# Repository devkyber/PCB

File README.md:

# PCB Copilot

**AI-assisted PCB engineering. Native KiCad. Evidence you can inspect.**

Prepare scoped changes, check the candidate, inspect the native views, and apply
it explicitly. Keep manufacturer evidence and engineering decisions with the
design through to a gated manufacturing package.

**[Get started](docs/QUICKSTART.md)** · **[Explore the examples](examples/README.md)** ·
**[Make an offline handover](docs/HANDOVER.md)** · **[Read the workflow](docs/WORKFLOW.md)**

## Follow a signal through three native boards

*Recorded native CAD renders and schematic captures of unbuilt prototypes.
All three report zero native ERC/DRC violations and zero unconnected items.
The USB-C PPTC body is not modeled. [Source and artifact hashes](docs/media/examples-manifest.json)
bind this gallery to the exact saved designs.*

| Example | Circuit and files | Current engineering boundary |
| --- | --- | --- |
| [USB-C power entry](examples/usb-c-power/README.md) | Six-contact USB4125 power-only connector, independent CC resistors, PPTC and transient shunt. [Schematic](examples/usb-c-power/output/schematic.pdf) · [3D model](examples/usb-c-power/output/usb-c-power.glb) | Native ERC/DRC and parity pass. Manufacturer lands meet the unchanged geometry baseline. Physical fit, protection behavior, assembly and human decisions remain open; no PD or current sensing. |
| [I²C temperature sensor](examples/i2c-sensor/README.md) | MCP9808 MSOP, eight selectable addresses and ALERT. [Schematic](examples/i2c-sensor/output/schematic.pdf) · [3D model](examples/i2c-sensor/output/i2c-sensor.glb) | Native ERC/DRC and parity pass. Bus behavior, physical fit, supplier assembly and human decisions remain open. |
| [RS-485 interface](examples/rs485-interface/README.md) | THVD1450, explicit control defaults and removable termination. [Schematic](examples/rs485-interface/output/schematic.pdf) · [3D model](examples/rs485-interface/output/rs485-interface.glb) | Native ERC/DRC and parity pass. Short bench-link prototype; isolation, surge/EMC and hardware behavior are unqualified. |

Each includes requirements, design basis, local libraries, exact manufacturer
archives, routed copper, native review views and a source-bound artifact
inventory. All remain **unbuilt DRAFTs**. The smaller
[GPIO indicator](examples/gpio-indicator/README.md) remains the first-run example.

The **[browser workbench](https://devkyber.github.io/PCB/)** needs no KiCad or
hardware connection. Search by reference or MPN, choose a numbered pin and
highlight its actual saved net. Inspect native copper, schematic and 3D views
beside the matching source evidence. The simplified net map omits pours and
exact pad shapes; the native copper views retain complete geometry.
[Download it for offline use or rebuild it](docs/EXPLORER.md).

Try the source-backed bring-up tools without hardware:

```sh
python examples/i2c-sensor/bringup.py demo
python examples/rs485-interface/bringup.py demo
```

The [sensor guide](examples/i2c-sensor/BRINGUP.md) covers identity, signed
big-endian temperature decoding, address shunts and ALERT configuration. The
[RS-485 guide](examples/rs485-interface/BRINGUP.md) covers termination load/power
bounds and explicit driver timing around the last UART stop bit. These are
checked calculations and transaction recipes, not recorded bench results.

## Get a first result

Use Git, **Python 3.11+** and
[uv](https://docs.astral.sh/uv/getting-started/installation/):

```sh
git clone https://github.com/devkyber/PCB.git
cd PCB
uv sync
uv run python tools/demo.py
```

The Python-only demo copies GPIO inputs into a new temporary directory, checks
status and archived bytes, and exercises the actual missing-preview rejection.
It prints an inspectable report, transcript and exact command logs while
preserving the saved source. Native ERC/DRC is separate.

Try a larger example with `--project examples/rs485-interface`. With **KiCad 10**
and its `pcbnew` Python bindings installed:

```sh
uv run pcb-copilot doctor
uv run python tools/demo.py --project examples/rs485-interface --full
```

A completed review with blockers returns **1** and preserves its findings.
[Quickstart](docs/QUICKSTART.md) covers setup, exit meanings and discovery.

## Hand an engineer an inspectable review

```sh
uv run pcb-copilot report examples/i2c-sensor --output NEW_EXTERNAL_DIRECTORY
uv run pcb-copilot verify-report NEW_EXTERNAL_DIRECTORY --project examples/i2c-sensor
```

Open the generated `index.html` offline. It includes every native schematic
page, assembly and mirrored copper views, the full review, check scopes and
source hashes. Filter findings, enlarge a view, and download the embedded vector
PDF. The packet's manifest also binds the original artifacts.

Verification runs without KiCad and distinguishes intact packet bytes from
whether the current project still matches. Viewing or verifying creates no
approval. See [the handover guide](docs/HANDOVER.md) and the recorded
[GPIO](docs/demos/gpio-review/index.html),
[sensor](docs/demos/i2c-review/index.html),
[RS-485](docs/demos/rs485-review/index.html) and
[USB-C](docs/demos/usb-c-review/index.html) packets.
Download the HTML to run it; GitHub displays its source.

## Inspect a successful change and a rejected stale apply

```sh
uv run python tools/demo_change.py
```

This prepares a real successful preview, changes the external candidate to
exercise stale-apply rejection, then creates a fresh preview. Inspect every
printed PDF page and use its exact hash-bound resume command to apply the
title-block revision to the disposable copy. Native electrical inventories,
PCB bytes and original source hashes are compared.
[The completed proof](docs/media/change-proof.md) records the actual
preview → stale rejection → fresh preview → reviewed apply sequence.

The [fault evaluation](docs/EVALUATION.md) tests corrupted evidence, changed
footprint geometry/model bytes, part identity, and independent candidate/source/
rule changes after genuine native previews:

```sh
uv run python tools/evaluate.py
uv run python tools/evaluate.py --native
uv run python tools/check_examples.py
```

Each case records its actual interface, diagnostic, exit and preservation
hashes. Native cases are explicitly skipped in quick mode. The example checker
verifies archives, selected-part coverage, footprint lineage and recorded
artifact identities; it does not rerun native qualification.

## Why this pipeline

| Engineering need | Implemented behavior |
| --- | --- |
| Preserve engineer-edited CAD | Start with saved native files. Scoped candidates preserve unrelated objects, UUIDs and routed copper. |
| Check where a part came from | Archive exact source bytes and verify selected MPNs, pad maps and local footprint/model receipts. |
| Inspect before installing | Preview with native-tool checks. Apply must match the current successful preview and all bound inputs. |
| Make review portable | Generate an offline handover with native views, complete findings and explicit check limits. |
| Keep decisions current | Bind named human decisions to CAD, requirements, rules and evidence; changed inputs invalidate them. |
| Preserve output during publication | Recheck sources and publish complete packages transactionally. Reject linked publication paths and retain recovery data when rollback cannot finish. |

```text
Saved KiCad + source evidence
             ↓
      Scoped candidate
             ↓
 Checks + native visual inspection
             ↓
       Explicit apply
             ↓
 Current human decisions → gated release
```

## Scope today

Native candidate preview/apply, evidence archive verification, exact supplier
part import, fourteen registered review checks, portable handovers and gated
manufacturing export are implemented. Optional autorouting needs Freerouting
and compatible Java; a route remains a candidate for review.

Agents can operate the CLI. A packaged interactive copilot/MCP service is future
work. Intent generation proposes a redraw and does not merge later manual CAD
edits. Autonomous engineering and measured time savings remain unproven.

The geometric house-rule checker covers portions of **4 of 42** historical
rule sections. ERC, DRC, parity and source hashes establish their stated scope;
circuit choices, thermal/RF/mechanical behavior, bench work and release decisions
still require engineering review. See [limitations](docs/LIMITATIONS.md).

## Use it with your project

Start with [the new-board workflow](docs/WORKFLOW.md#start-a-new-board) and
`templates/project/`. For an existing design, save and close KiCad, prepare a
separate native candidate and preview before using the identical command with
`--apply`. The [complete workflow](docs/WORKFLOW.md) covers layout, supplier
assembly, sign-off and recovery.

Read [Rover PDB](projects/rover-pdb/README.md) and [TMS](projects/tms/README.md)
for those owner projects' recorded status. Their saved CAD and requested scope
remain separate from the educational examples. Frozen boards under
`tests/fixtures/boards` are regression inputs.

| Read | Purpose |
| --- | --- |
| [Quickstart](docs/QUICKSTART.md) | Setup and first useful result |
| [Example catalog](examples/README.md) | Circuits, assumptions and native artifacts |
| [Interactive explorer](docs/EXPLORER.md) | Follow native pads/nets, inspect views and source evidence |
| [Handover](docs/HANDOVER.md) | Generate and verify offline review packets |
| [Workflow](docs/WORKFLOW.md) | Preview, apply, review and release |
| [Architecture](docs/ARCHITECTURE.md) | Ownership and implementation boundaries |
| [Design rules](docs/DESIGN_RULES.md) | Drawing, layout and review conventions |
| [Fault evaluation](docs/EVALUATION.md) | Reproduce the declared regression cases |
| [Roadmap](docs/ROADMAP.md) | Next capabilities and acceptance evidence |
| [Media sources](docs/media/README.md) | Reproduce the images and video |

If the workflow is useful, a star helps other engineers discover it.

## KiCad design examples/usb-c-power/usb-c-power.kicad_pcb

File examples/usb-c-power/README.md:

# USB-C 5 V bench power entry

An **unbuilt educational DRAFT** with independent CC pull-downs, a resettable
fuse, a unidirectional TVS, a power LED and a two-pin output. The
60 × 40 mm two-layer board is fully routed. Revision B replaces the original
connector with the six-contact, power-only GCT USB4125-GF-A: native ERC and
refilled DRC now report zero findings under the unchanged manufacturing rules.
Actual assembly, physical fit and hardware behavior remain unqualified.

Open [usb-c-power.kicad_pro](usb-c-power.kicad_pro) in KiCad 10, or inspect the
[schematic PDF](output/schematic.pdf), [schematic image](output/schematic.png),
[assembly drawing](output/assembly.png), [front copper](output/top-copper.png),
[mirrored underside](output/bottom-copper.png) and [native GLB](output/usb-c-power.glb).
F1 intentionally has no 3D body model. The other package models are exact
archived KiCad library models; none qualifies the selected part's physical fit.

From the repository root:

```sh
uv run pcb-copilot status examples/usb-c-power
uv run pcb-copilot research examples/usb-c-power --verify
uv run pcb-copilot research examples/usb-c-power --verify-schematic-parts
uv run pcb-copilot review examples/usb-c-power --format json
```

The review returns **exit 1**. The dated [actual review](output/review-b.json)
reports clean native ERC/refilled DRC, exact schematic/PCB part/pin-net/UUID
parity and zero unrouted connections. The former eight connector errors were
resolved by selecting compatible manufacturer geometry: 0.25 mm shell rings
and no locating-peg holes. No rule was relaxed, finding excluded, contact land
trimmed, reference waiver added, or human approval invented. Supplier assembly
contracts, the F1 body model and all six human decisions remain unresolved.

Use only a separately qualified **4.75–5.25 V bench source and at most 500 mA
total board-plus-load budget near 23 °C**. Passive 5.1 kOhm CC pull-downs do not
negotiate PD or establish permission to draw 500 mA from every USB port. There
is no source-current detector, active current limiter, reverse blocking,
output regulator or inrush controller. Never backfeed J2. Its pin1 is VOUT and
pin2 is GND; VOUT includes fuse/connector/copper voltage loss.

The selected 0.75 A hold PPTC is **not a 500 mA current limiter**. The TVS has
6 V standoff and a listed 10.3 V maximum clamp at its specified pulse test;
it does **not** provide 5 V overvoltage protection for sensitive loads. Start
with a non-sensitive resistive dummy load and current-limited source. Reflow
is required for the selected PPTC assembly plan. The [design basis](DESIGN_BASIS.md)
records exact manufacturer limits, calculations, pad mapping and open tests.

[Evidence](evidence/index.yaml) archives all selected purchased-part PDFs,
the dated USB integration reference and a pinned Adafruit open-hardware
schematic/board pair for comparison. The [reference review](REFERENCE_REVIEW.md)
states the adopted pattern and differences. The [official-copy receipt](libs/PROVENANCE.json)
and separate [Bourns drawing receipt](libs/footprint-provenance.yaml) pass their
scoped lineage checks. Bourns' recommended PPTC lands differ from generic
1812 pads, so F1 uses an explicitly derived footprint. The replacement USB4125
uses exact official footprint/model copies. All other footprints, every existing
via and unrelated tracks are preserved; J1's local escapes are routed to its
actual six contact positions.

[SOURCE.json](output/SOURCE.json) binds the retained outputs, exact saved
inputs, native version and raw command logs. Checks and renders ran on an
external disposable copy, with source and snapshot input hashes unchanged.
The [author review](docs/review/B_REVIEW.md) records actual page and layout
inspection; it is not an owner sign-off or a hardware qualification.

Saved native CAD is authoritative. Use a separate copy for experiments and
the [shared candidate workflow](../../docs/WORKFLOW.md) for revisions. No owner
board, existing example CAD or frozen test fixture was used as this design's
starting circuit or layout.

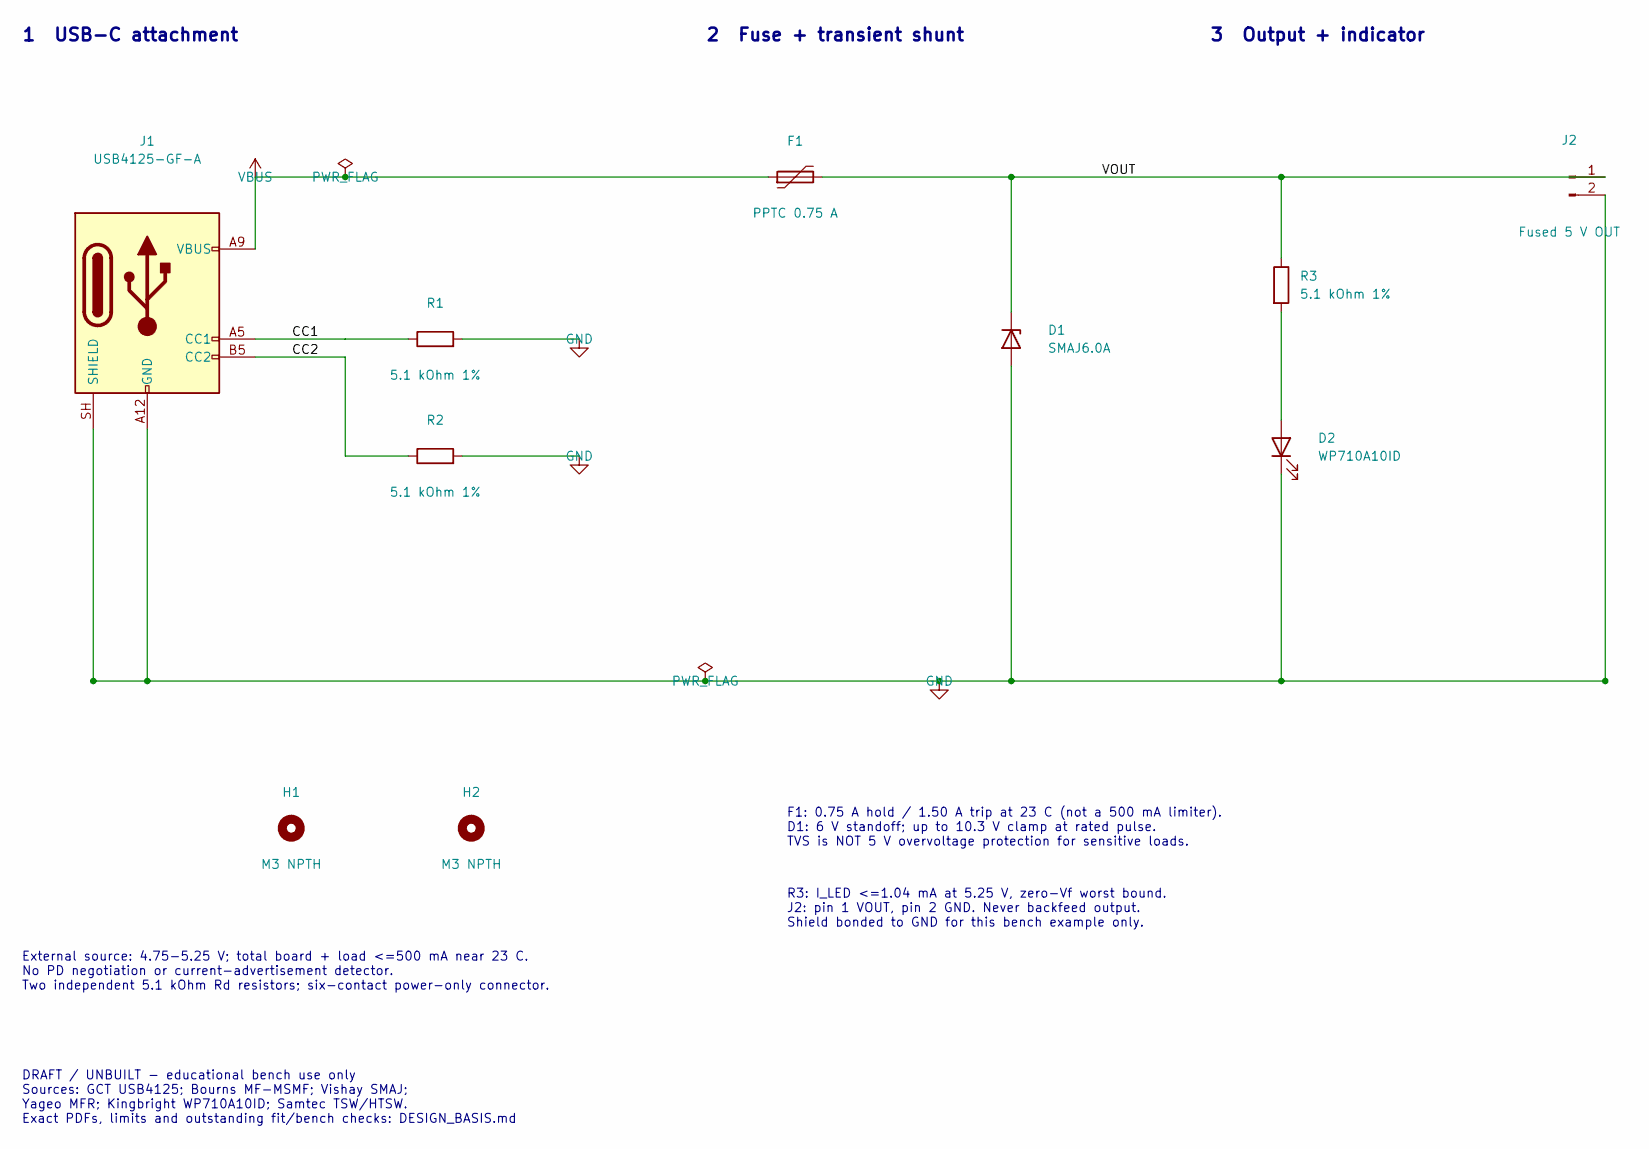
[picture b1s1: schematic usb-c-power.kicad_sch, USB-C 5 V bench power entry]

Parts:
D1: SMAJ6.0A; D_SMA; MPN SMAJ6.0A
D2: WP710A10ID; LED_D3.0mm; MPN WP710A10ID
F1: PPTC 0.75 A; MF-MSMF075_1812_Style1; MPN MF-MSMF075-2
H1, H2: M3 NPTH; MountingHole_3.2mm_M3
J1: USB4125-GF-A; USB_C_Receptacle_GCT_USB4125-xx-x_6P_TopMnt_Horizontal; MPN USB4125-GF-A
J2: Fused 5 V OUT; PinHeader_1x02_P2.54mm_Vertical; MPN HTSW-102-07-G-S
R1, R2, R3: 5.1 kOhm 1%; R_Axial_DIN0207_L6.3mm_D2.5mm_P10.16mm_Horizontal; MPN MFR-25FBF52-5K1

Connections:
CC1: J1.A5 (CC1), R1.1
CC2: J1.B5 (CC2), R2.1
GND: D1.2 (A), D2.1 (K), J1.A12 (GND), J1.B12 (GND), J1.SH (SHIELD), J2.2, R1.2, R2.2
unnamed: D2.2 (A), R3.2
VBUS: F1.1, J1.A9 (VBUS), J1.B9 (VBUS)
VOUT: D1.1 (K), F1.2, J2.1, R3.1

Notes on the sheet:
1 USB-C attachment
2 Fuse + transient shunt
3 Output + indicator
External source: 4.75-5.25 V; total board + load <=500 mA near 23 C. No PD negotiation or current-advertisement detector. Two independent 5.1 kOhm Rd resistors; six-contact power-only connector.
F1: 0.75 A hold / 1.50 A trip at 23 C (not a 500 mA limiter). D1: 6 V standoff; up to 10.3 V clamp at rated pulse. TVS is NOT 5 V overvoltage protection for sensitive loads.
R3: I_LED <=1.04 mA at 5.25 V, zero-Vf worst bound. J2: pin 1 VOUT, pin 2 GND. Never backfeed output. Shield bonded to GND for this bench example only.
DRAFT / UNBUILT - educational bench use only Sources: GCT USB4125; Bourns MF-MSMF; Vishay SMAJ; Yageo MFR; Kingbright WP710A10ID; Samtec TSW/HTSW. Exact PDFs, limits and outstanding fit/bench checks: DESIGN_BASIS.md

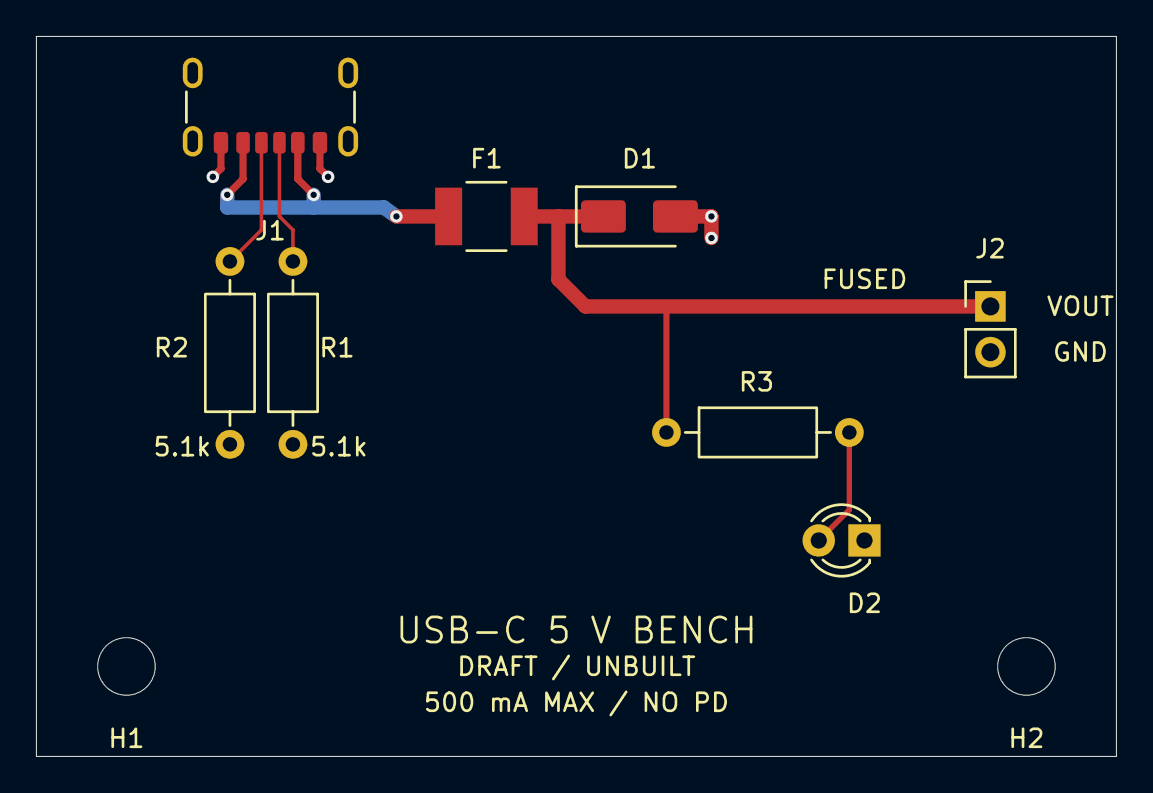
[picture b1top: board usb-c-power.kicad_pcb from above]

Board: 2 copper layers, 60.0 x 40.0 mm, 10 parts (0 on the bottom side), 6 nets.

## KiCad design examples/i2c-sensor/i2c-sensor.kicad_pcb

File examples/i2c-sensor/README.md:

# I2C temperature sensor

An editable 3.3 V MCP9808 MSOP breakout: eight selectable I2C addresses, a local ceramic bypass, fixed bus pullups and a separate open-drain ALERT header. Unbuilt DRAFT; no owner or fabrication approval.

[Start with the register bring-up guide](BRINGUP.md): decode MSB-first signed
temperature words, verify identity/address, and produce a checked ALERT write
recipe. Run the CLI from the repository root; it works offline with no hardware dependency:

```sh
python examples/i2c-sensor/bringup.py decode 0194
python examples/i2c-sensor/bringup.py address --a0 1 --a2 1
```

The example bytes decode to +25.25 C and address 0x1D. These are software
examples, not readings from this unbuilt board. A small read-only bus adapter is
provided for an explicitly configured host; locked settings and malformed reads
are rejected rather than silently accepted.

J1 is 3V3 / GND / SCL / SDA. JP1..3 select A0..A2; no shunts gives 0x18. Power off before changing address shunts. Start at 100 kHz and assess the real host's voltage, combined pullups and measured bus rise time. ALERT requires firmware configuration after reset.

The root KiCad files are the editable design. REQUIREMENTS.md defines the operating assumptions; DESIGN_BASIS.md records exact source decisions and calculations. evidence/index.yaml binds archived primary manufacturer bytes. Local official KiCad library copies, models and license/source receipts are in libs/. Generic mechanical models and a clean native check do not qualify physical fit, temperature accuracy or assembly.

```powershell
uv run pcb-copilot review examples/i2c-sensor
uv run pcb-copilot report examples/i2c-sensor --output C:/Temp/i2c-sensor-handover
```

Retained native views/check results in output/ are bound to declared source hashes by SOURCE.json. Any source change requires fresh checks and views. Full review deliberately remains blocked by unsigned human decisions and missing supplier assembly contracts. No fabrication outputs or bench results are included.

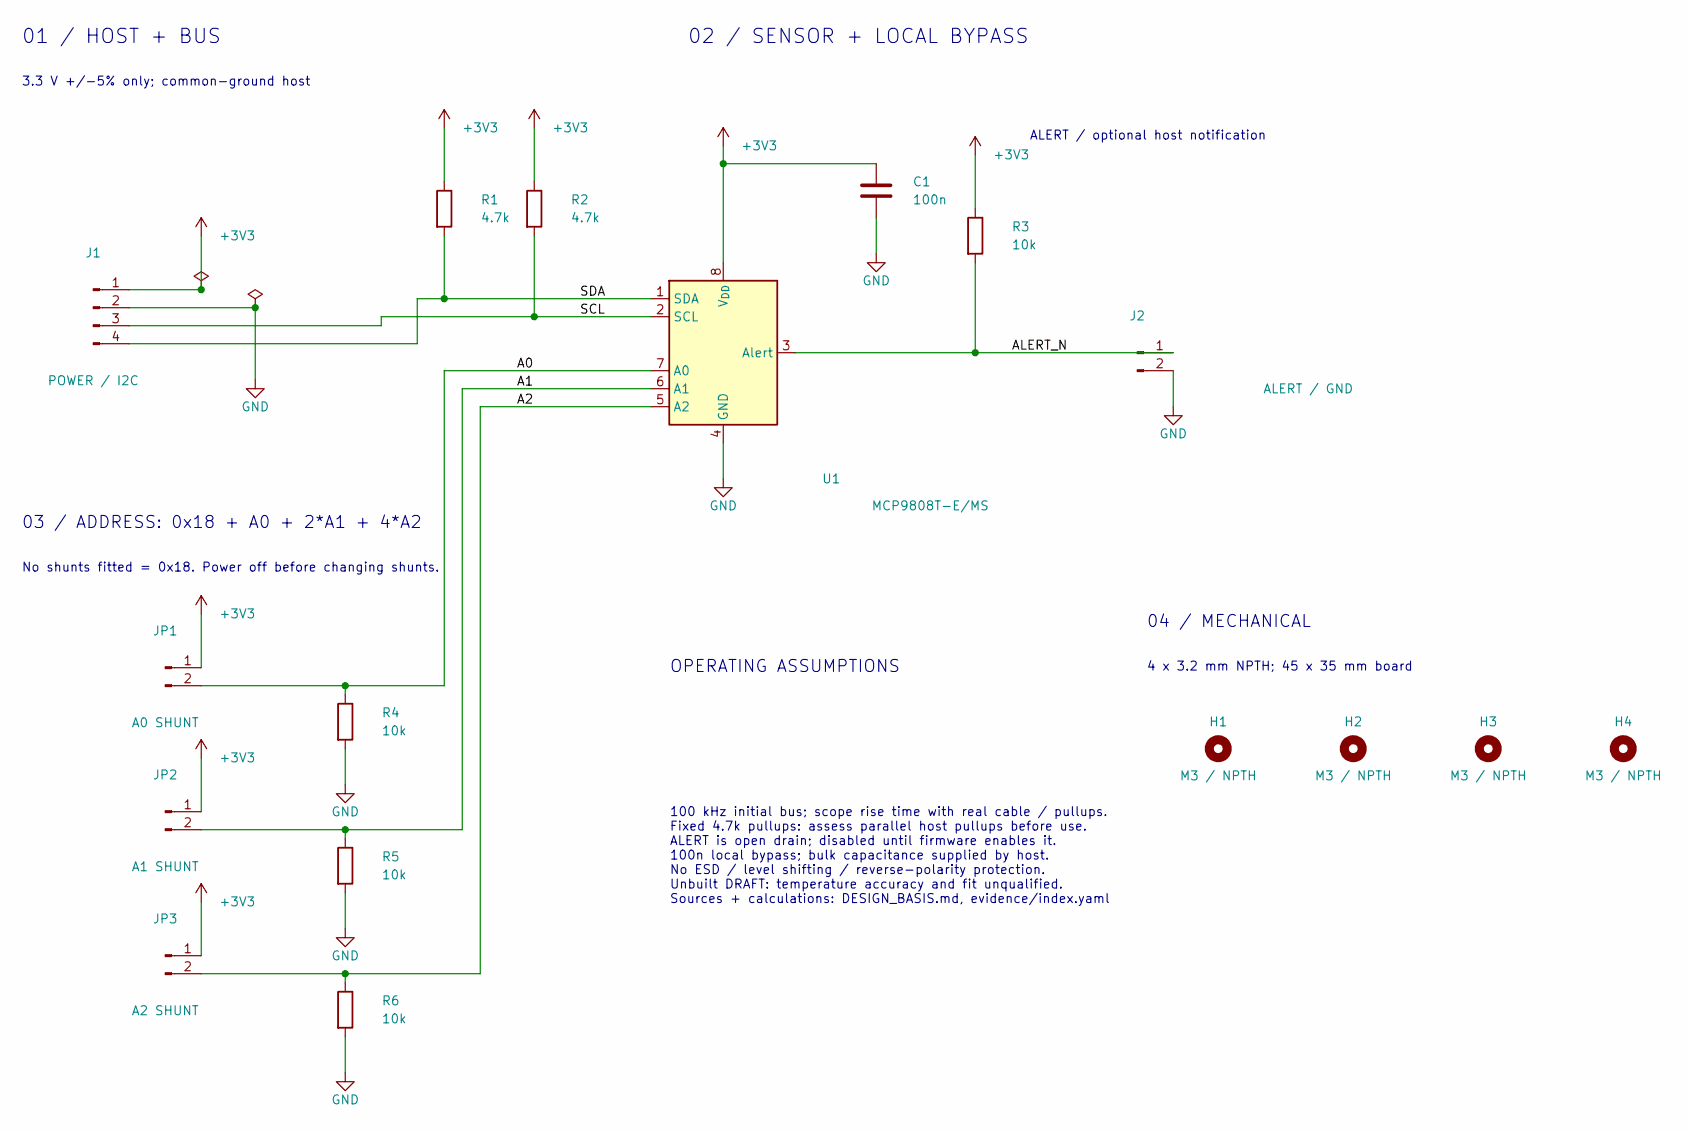
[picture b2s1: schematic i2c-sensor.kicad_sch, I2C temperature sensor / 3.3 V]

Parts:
C1: 100n; C0805_100N; MPN C0805C104K5RACTU
H1, H2, H3, H4: M3 / NPTH; MountingHole_3.2mm_M3
J1: POWER / I2C; Header4_61300411121; MPN 61300411121
J2: ALERT / GND; Header2_61300211121; MPN 61300211121
JP1: A0 SHUNT; Header2_61300211121; MPN 61300211121
JP2: A1 SHUNT; Header2_61300211121; MPN 61300211121
JP3: A2 SHUNT; Header2_61300211121; MPN 61300211121
R1, R2: 4.7k; R0805_4K7; MPN RC0805FR-074K7L
R3, R4, R5, R6: 10k; R0805_10K; MPN RC0805FR-0710KL
U1: MCP9808T-E/MS; MSOP8_MCP9808; MPN MCP9808T-E/MS

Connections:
+3V3: C1.1, J1.1, JP1.1, JP2.1, JP3.1, R1.1, R2.1, R3.1, U1.8 (V_{DD})
A0: JP1.2, R4.1, U1.7 (A0)
A1: JP2.2, R5.1, U1.6 (A1)
A2: JP3.2, R6.1, U1.5 (A2)
ALERT_N: J2.1, R3.2, U1.3 (Alert)
GND: C1.2, J1.2, J2.2, R4.2, R5.2, R6.2, U1.4 (GND)
SCL: J1.3, R2.2, U1.2 (SCL)
SDA: J1.4, R1.2, U1.1 (SDA)

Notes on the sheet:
01 / HOST + BUS
3.3 V +/-5% only; common-ground host
02 / SENSOR + LOCAL BYPASS
03 / ADDRESS: 0x18 + A0 + 2*A1 + 4*A2
No shunts fitted = 0x18. Power off before changing shunts.
04 / MECHANICAL
4 x 3.2 mm NPTH; 45 x 35 mm board
OPERATING ASSUMPTIONS
100 kHz initial bus; scope rise time with real cable / pullups. Fixed 4.7k pullups: assess parallel host pullups before use. ALERT is open drain; disabled until firmware enables it. 100n local bypass; bulk capacitance supplied by host. No ESD / level shifting / reverse-polarity protection. Unbuilt 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
ALERT / optional host notification

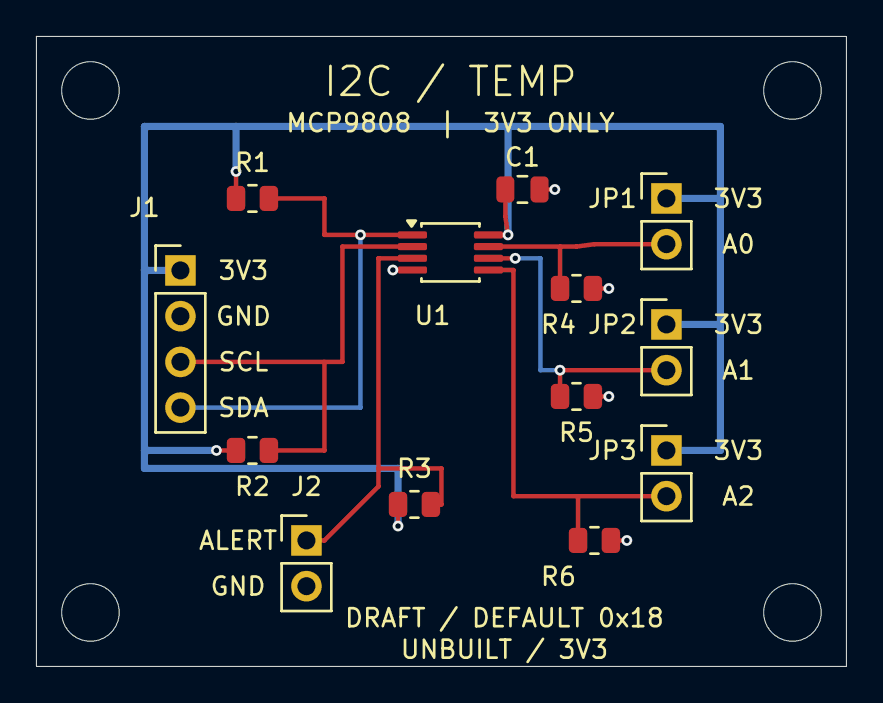
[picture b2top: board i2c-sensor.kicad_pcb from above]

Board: 2 copper layers, 45.0 x 35.0 mm, 17 parts (0 on the bottom side), 8 nets.

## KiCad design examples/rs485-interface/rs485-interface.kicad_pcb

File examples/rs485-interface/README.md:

# 3.3 V RS-485 interface

**Unbuilt educational DRAFT.** A native KiCad UART-to-half-duplex-RS-485 board
with a TI THVD1450DR, independent driver/receiver controls and removable end
termination. No isolation, industrial ESD/surge/EMC, physical-fit or link-speed
qualification is claimed. Nothing here is approval to fabricate or energize.

[Follow the bring-up guide](BRINGUP.md) for connector wiring, removable
termination, default receive, local echo and the exact DE/nRE sequence around the
last UART stop bit. Run these offline tools from the repository root; they access
no serial port or GPIO:

```sh
python examples/rs485-interface/bringup.py budget --supply 3.3 --terminations 2
python examples/rs485-interface/bringup.py sequence --bytes 4 --suppress-echo
```

The termination-only model exposes missing/excess termination and the conservative
current boundary at 3.6 V. Its serialization estimate never replaces the actual
controller's hardware TX-complete flag. Tests and retained demo output contain no
measured hardware result.

| Property | Design |
| --- | --- |
| PCB | 50 x 35 mm, two layers, four 3.2 mm NPTH mounting holes |
| Supply/logic | External 3.3 V nominal, project input 3.0-3.6 V |
| Transceiver | THVD1450DR, SOIC-8; no MCU or firmware included |
| J1 | 1=3V3, 2=GND, 3=TXD into board, 4=RXD out, 5=DE, 6=nRE |
| J2 | 1=A, 2=B, 3=GND; names follow TI |
| Default | R1/R2 10 kOhm: driver disabled, receiver enabled when host floats |
| Termination | R3 120 Ohm/1%/0.25 W; JP1 shunt only at a physical cable end |
| Accessory | Samtec SNT-100-BK-G shunt, separate off-board item; not installed in the native 3D model |

Use compatible 3.3 V host logic, a shared reference ground and an appropriate
short twisted pair for initial bench evaluation. Confirm the other node's A/B
convention. Fit termination at both physical cable ends as required by the cable;
remove JP1 at middle nodes. Host, supply, cable and remote node remain unselected.
115200 baud is an initial test target, not a demonstrated rating. Fast edges
still need proper line treatment even at low baud rates.

Open [the native project](rs485-interface.kicad_pro),
[schematic](rs485-interface.kicad_sch) and [PCB](rs485-interface.kicad_pcb).
The saved CAD is authoritative; authoring scratch files are ignored and must
never be replayed over later owner edits. Native footprint UUID links preserve
ordinary forward annotation. See [requirements](REQUIREMENTS.md),
[design basis](DESIGN_BASIS.md), [reference comparison](REFERENCE_REVIEW.md),
[source index](evidence/index.yaml) and [library provenance](libs/README.md).

Inspect [the schematic PDF](output/schematic.pdf),
[front copper](output/front.png), [mirrored back](output/back.png),
[assembly drawing](output/assembly.png), [native model](output/rs485-interface.glb)
and [author inspection](docs/review/A1_REVIEW.md). Every page and board view
needs actual visual review; an export or clean ERC/DRC alone is insufficient.

From the repository root:

```sh
uv run pcb-copilot research examples/rs485-interface --verify
uv run pcb-copilot research examples/rs485-interface --verify-schematic-parts
uv run pcb-copilot review examples/rs485-interface --format json
```

The [saved review](output/review.json) records its actual checks and remaining
blockers. Missing exact supplier assembly contracts and unsigned human decisions
must remain visible. No owner sign-off, placement approval, hardware test or
fabrication release is supplied. [Source/output hashes](output/SOURCE.json)
identify the particular retained renders and software results.

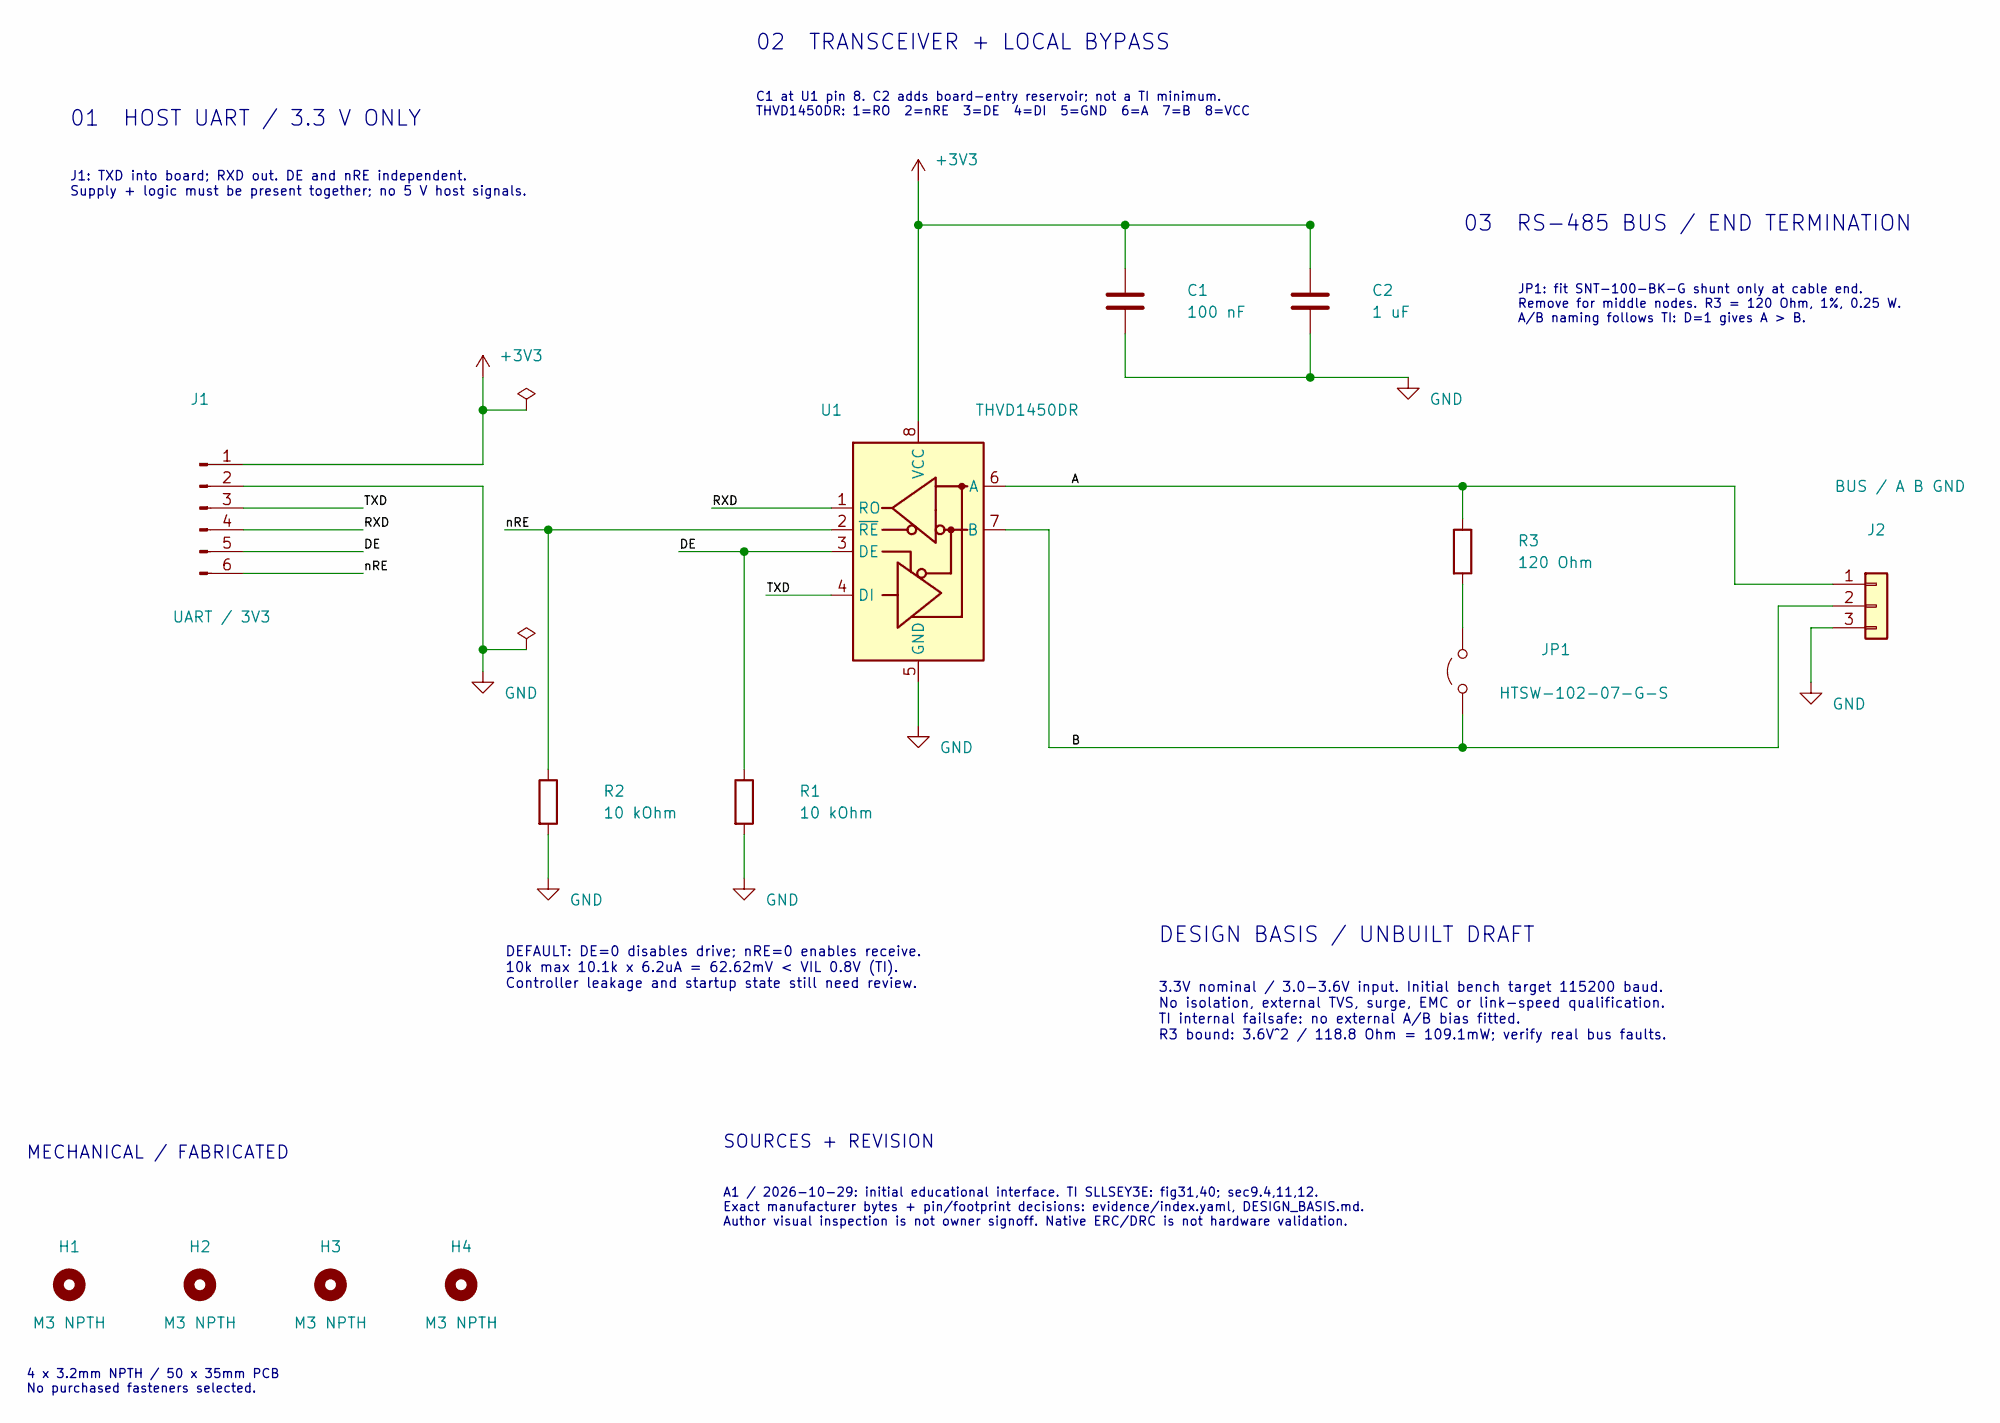
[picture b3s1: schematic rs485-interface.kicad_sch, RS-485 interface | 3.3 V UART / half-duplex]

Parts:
C1: 100 nF; C0805_100nF; MPN CC0805KRX7R9BB104
C2: 1 uF; C0805_1uF; MPN CC0805KKX7R7BB105
H1, H2, H3, H4: M3 NPTH; MountingHole_3.2mm_M3
J1: UART / 3V3; UART_HTSW106; MPN HTSW-106-07-G-S
J2: BUS / A B GND; BUS_HTSW103; MPN HTSW-103-07-G-S
JP1: HTSW-102-07-G-S; TERM_HTSW102; MPN HTSW-102-07-G-S
R1, R2: 10 kOhm; R0805_10k; MPN CRCW080510K0FKEA
R3: 120 Ohm; R1206_120R; MPN CRCW1206120RFKEA
U1: THVD1450DR; SOIC8_THVD1450DR; MPN THVD1450DR

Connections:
+3V3: C1.1, C2.1, J1.1, U1.8 (VCC)
A: J2.1, R3.1, U1.6 (A)
B: J2.2, JP1.1 (A), U1.7 (B)
DE: J1.5, R1.1, U1.3 (DE)
GND: C1.2, C2.2, J1.2, J2.3, R1.2, R2.2, U1.5 (GND)
unnamed: JP1.2 (B), R3.2
RXD: J1.4, U1.1 (RO)
TXD: J1.3, U1.4 (DI)
nRE: J1.6, R2.1, U1.2 (~RE)

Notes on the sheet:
01 HOST UART / 3.3 V ONLY
J1: TXD into board; RXD out. DE and nRE independent. Supply + logic must be present together; no 5 V host signals.
02 TRANSCEIVER + LOCAL BYPASS
C1 at U1 pin 8. C2 adds board-entry reservoir; not a TI minimum. THVD1450DR: 1=RO 2=nRE 3=DE 4=DI 5=GND 6=A 7=B 8=VCC
03 RS-485 BUS / END TERMINATION
JP1: fit SNT-100-BK-G shunt only at cable end. Remove for middle nodes. R3 = 120 Ohm, 1%, 0.25 W. A/B naming follows TI: D=1 gives A > B.
DEFAULT: DE=0 disables drive; nRE=0 enables receive. 10k max 10.1k x 6.2uA = 62.62mV < VIL 0.8V (TI). Controller leakage and startup state still need review.
DESIGN BASIS / UNBUILT DRAFT
3.3V nominal / 3.0-3.6V input. Initial bench target 115200 baud. No isolation, external TVS, surge, EMC or link-speed qualification. TI internal failsafe: no external A/B bias fitted. R3 bound: 3.6V^2 / 118.8 Ohm = 109.1mW; verify real bus faults.
MECHANICAL / FABRICATED
4 x 3.2mm NPTH / 50 x 35mm PCB No purchased fasteners selected.
SOURCES + REVISION
A1 / 2026-10-29: initial educational interface. TI SLLSEY3E: fig31,40; sec9.4,11,12. Exact manufacturer bytes + pin/footprint decisions: evidence/index.yaml, DESIGN_BASIS.md. Author visual inspection is not owner signoff. Native ERC/DRC is not hardware validation.

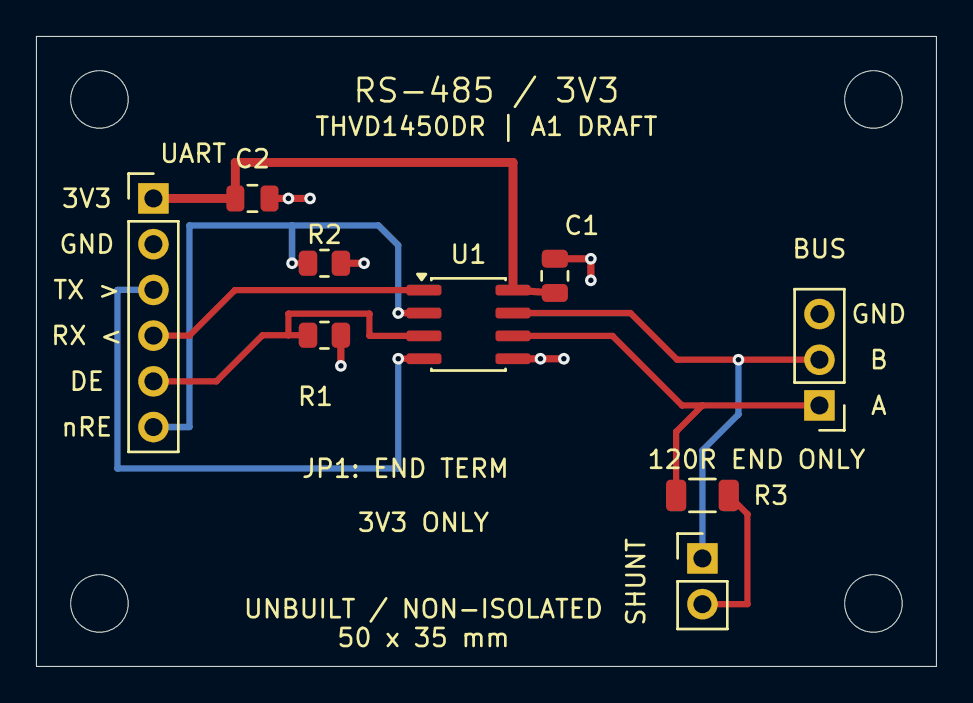
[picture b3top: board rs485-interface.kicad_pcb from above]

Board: 2 copper layers, 50.0 x 35.0 mm, 13 parts (0 on the bottom side), 9 nets.

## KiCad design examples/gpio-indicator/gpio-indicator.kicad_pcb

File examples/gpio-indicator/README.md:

# Four-channel GPIO indicator

An **unbuilt educational DRAFT** for trying PCB Copilot on a complete, small KiCad design. Four independent 0 to 3.3 V inputs drive four red LEDs through 1.1 kOhm resistors. The 45 x 35 mm board has two copper layers, through-hole components, two mounting holes, project-local libraries and all three package models.

Open [gpio-indicator.kicad_pro](gpio-indicator.kicad_pro) in KiCad 10, or inspect the [schematic PDF](output/schematic.pdf), [schematic image](output/schematic.png), [assembly drawing](output/assembly.png), [front copper](output/top-copper.png) and [mirrored underside](output/bottom-copper.png). The [GLB model](output/gpio-indicator.glb) is a native CAD visualization; it does not establish actual component fit.

From the repository root:

```sh
uv run pcb-copilot doctor
uv run pcb-copilot status examples/gpio-indicator
uv run pcb-copilot research examples/gpio-indicator --verify
uv run pcb-copilot research examples/gpio-indicator --verify-schematic-parts
uv run pcb-copilot review examples/gpio-indicator
```

The last command deliberately returns **exit 1**: supplier assembly rotation contracts and all five human review decisions are absent. Native ERC and DRC are clean, connectivity and forward-annotation links agree, and the independent dated JLCPCB geometry check passes. These results are scoped machine checks, not fabrication approval or measured performance. See the [saved review](output/review-a1.json) and [author inspection record](docs/review/A1_REVIEW.md).

J1 pins 1 through 4 are IN1 through IN4; pin 5 is GND. It has no power pin. With a 3.3 V input and initial 1% resistance tolerance, the calculation gives at most **3.031 mA per channel**, taking no credit for LED forward voltage. That loading must suit the actual controller's per-pin and aggregate drive limits. Actual brightness, current, fit, assembly and external-controller behavior remain unqualified.

The resistor was deliberately chosen as 1.1 kOhm: 1 kOhm at its negative 1% tolerance would allow a 3.333 mA zero-Vf bound. The [requirements](REQUIREMENTS.md) and [design basis](DESIGN_BASIS.md) state the assumptions and scope. This example has no ESD protection, isolation, level conversion, voltage regulation or approval for an application.

Exact manufacturer PDF bytes are in [evidence](evidence/index.yaml). The [library receipt](libs/PROVENANCE.json) binds official KiCad footprint copies, pad functions, manufacturer evidence and local model bytes to their hashes. The local footprint files change only model URIs. Board instances use wider silkscreen strokes to meet the workspace baseline; numbered pad geometry is unchanged. Generic package models are visualization aids.

The saved native CAD is authoritative. A construction script must not overwrite later edits. Use a separate copy for experiments and the [shared candidate workflow](../../docs/WORKFLOW.md) for checked updates. No owner board or frozen test fixture was modified to create this example.

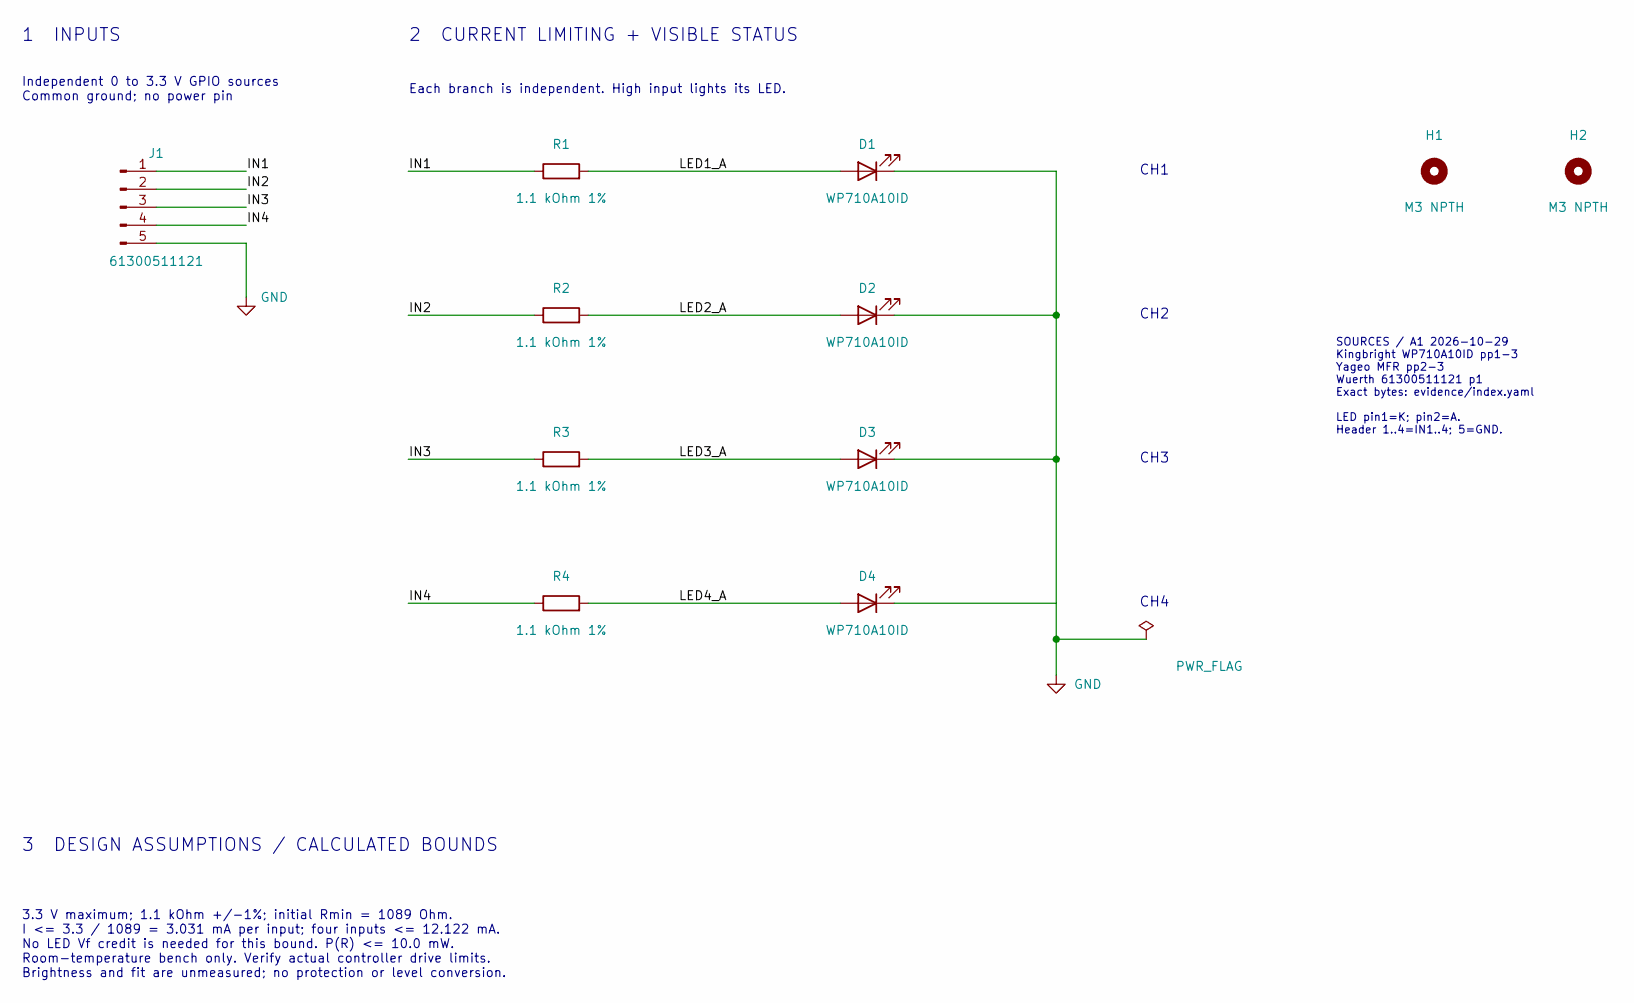
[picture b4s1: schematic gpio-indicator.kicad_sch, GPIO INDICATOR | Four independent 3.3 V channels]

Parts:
D1, D2, D3, D4: WP710A10ID; LED_D3.0mm; MPN WP710A10ID
H1, H2: M3 NPTH; MountingHole_3.2mm_M3
J1: 61300511121; PinHeader_1x05_P2.54mm_Vertical; MPN 61300511121
R1, R2, R3, R4: 1.1 kOhm 1%; R_Axial_DIN0207_L6.3mm_D2.5mm_P10.16mm_Horizontal; MPN MFR-25FBF52-1K1

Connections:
/IN1: J1.1, R1.1
/IN2: J1.2, R2.1
/IN3: J1.3, R3.1
/IN4: J1.4, R4.1
/LED1_A: D1.2 (A), R1.2
/LED2_A: D2.2 (A), R2.2
/LED3_A: D3.2 (A), R3.2
/LED4_A: D4.2 (A), R4.2
GND: D1.1 (K), D2.1 (K), D3.1 (K), D4.1 (K), J1.5

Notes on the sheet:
1 INPUTS
Independent 0 to 3.3 V GPIO sources Common ground; no power pin
2 CURRENT LIMITING + VISIBLE STATUS
Each branch is independent. High input lights its LED.
CH1
CH2
CH3
CH4
3 DESIGN ASSUMPTIONS / CALCULATED BOUNDS
3.3 V maximum; 1.1 kOhm +/-1%; initial Rmin = 1089 Ohm. I <= 3.3 / 1089 = 3.031 mA per input; four inputs <= 12.122 mA. No LED Vf credit is needed for this bound. P(R) <= 10.0 mW. Room-temperature bench only. Verify actual controller drive limits. Brightness and fit are unmeasured; no protection or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
SOURCES / A1 2026-10-29 Kingbright WP710A10ID pp1-3 Yageo MFR pp2-3 Wuerth 61300511121 p1 Exact bytes: evidence/index.yaml LED pin1=K; pin2=A. Header 1..4=IN1..4; 5=GND.

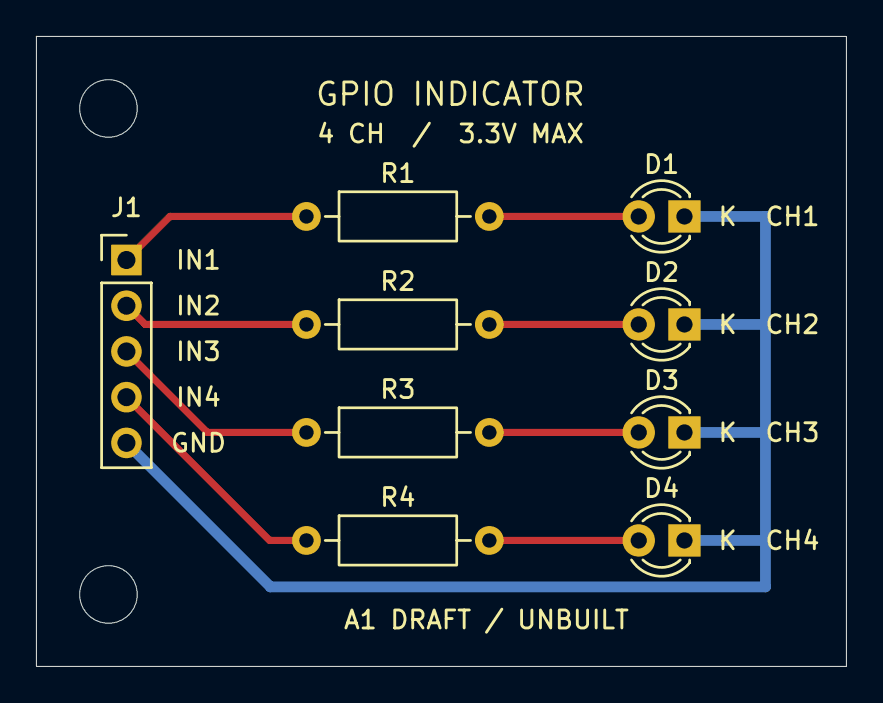
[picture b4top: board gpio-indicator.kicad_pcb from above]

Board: 2 copper layers, 45.0 x 35.0 mm, 11 parts (0 on the bottom side), 9 nets.
